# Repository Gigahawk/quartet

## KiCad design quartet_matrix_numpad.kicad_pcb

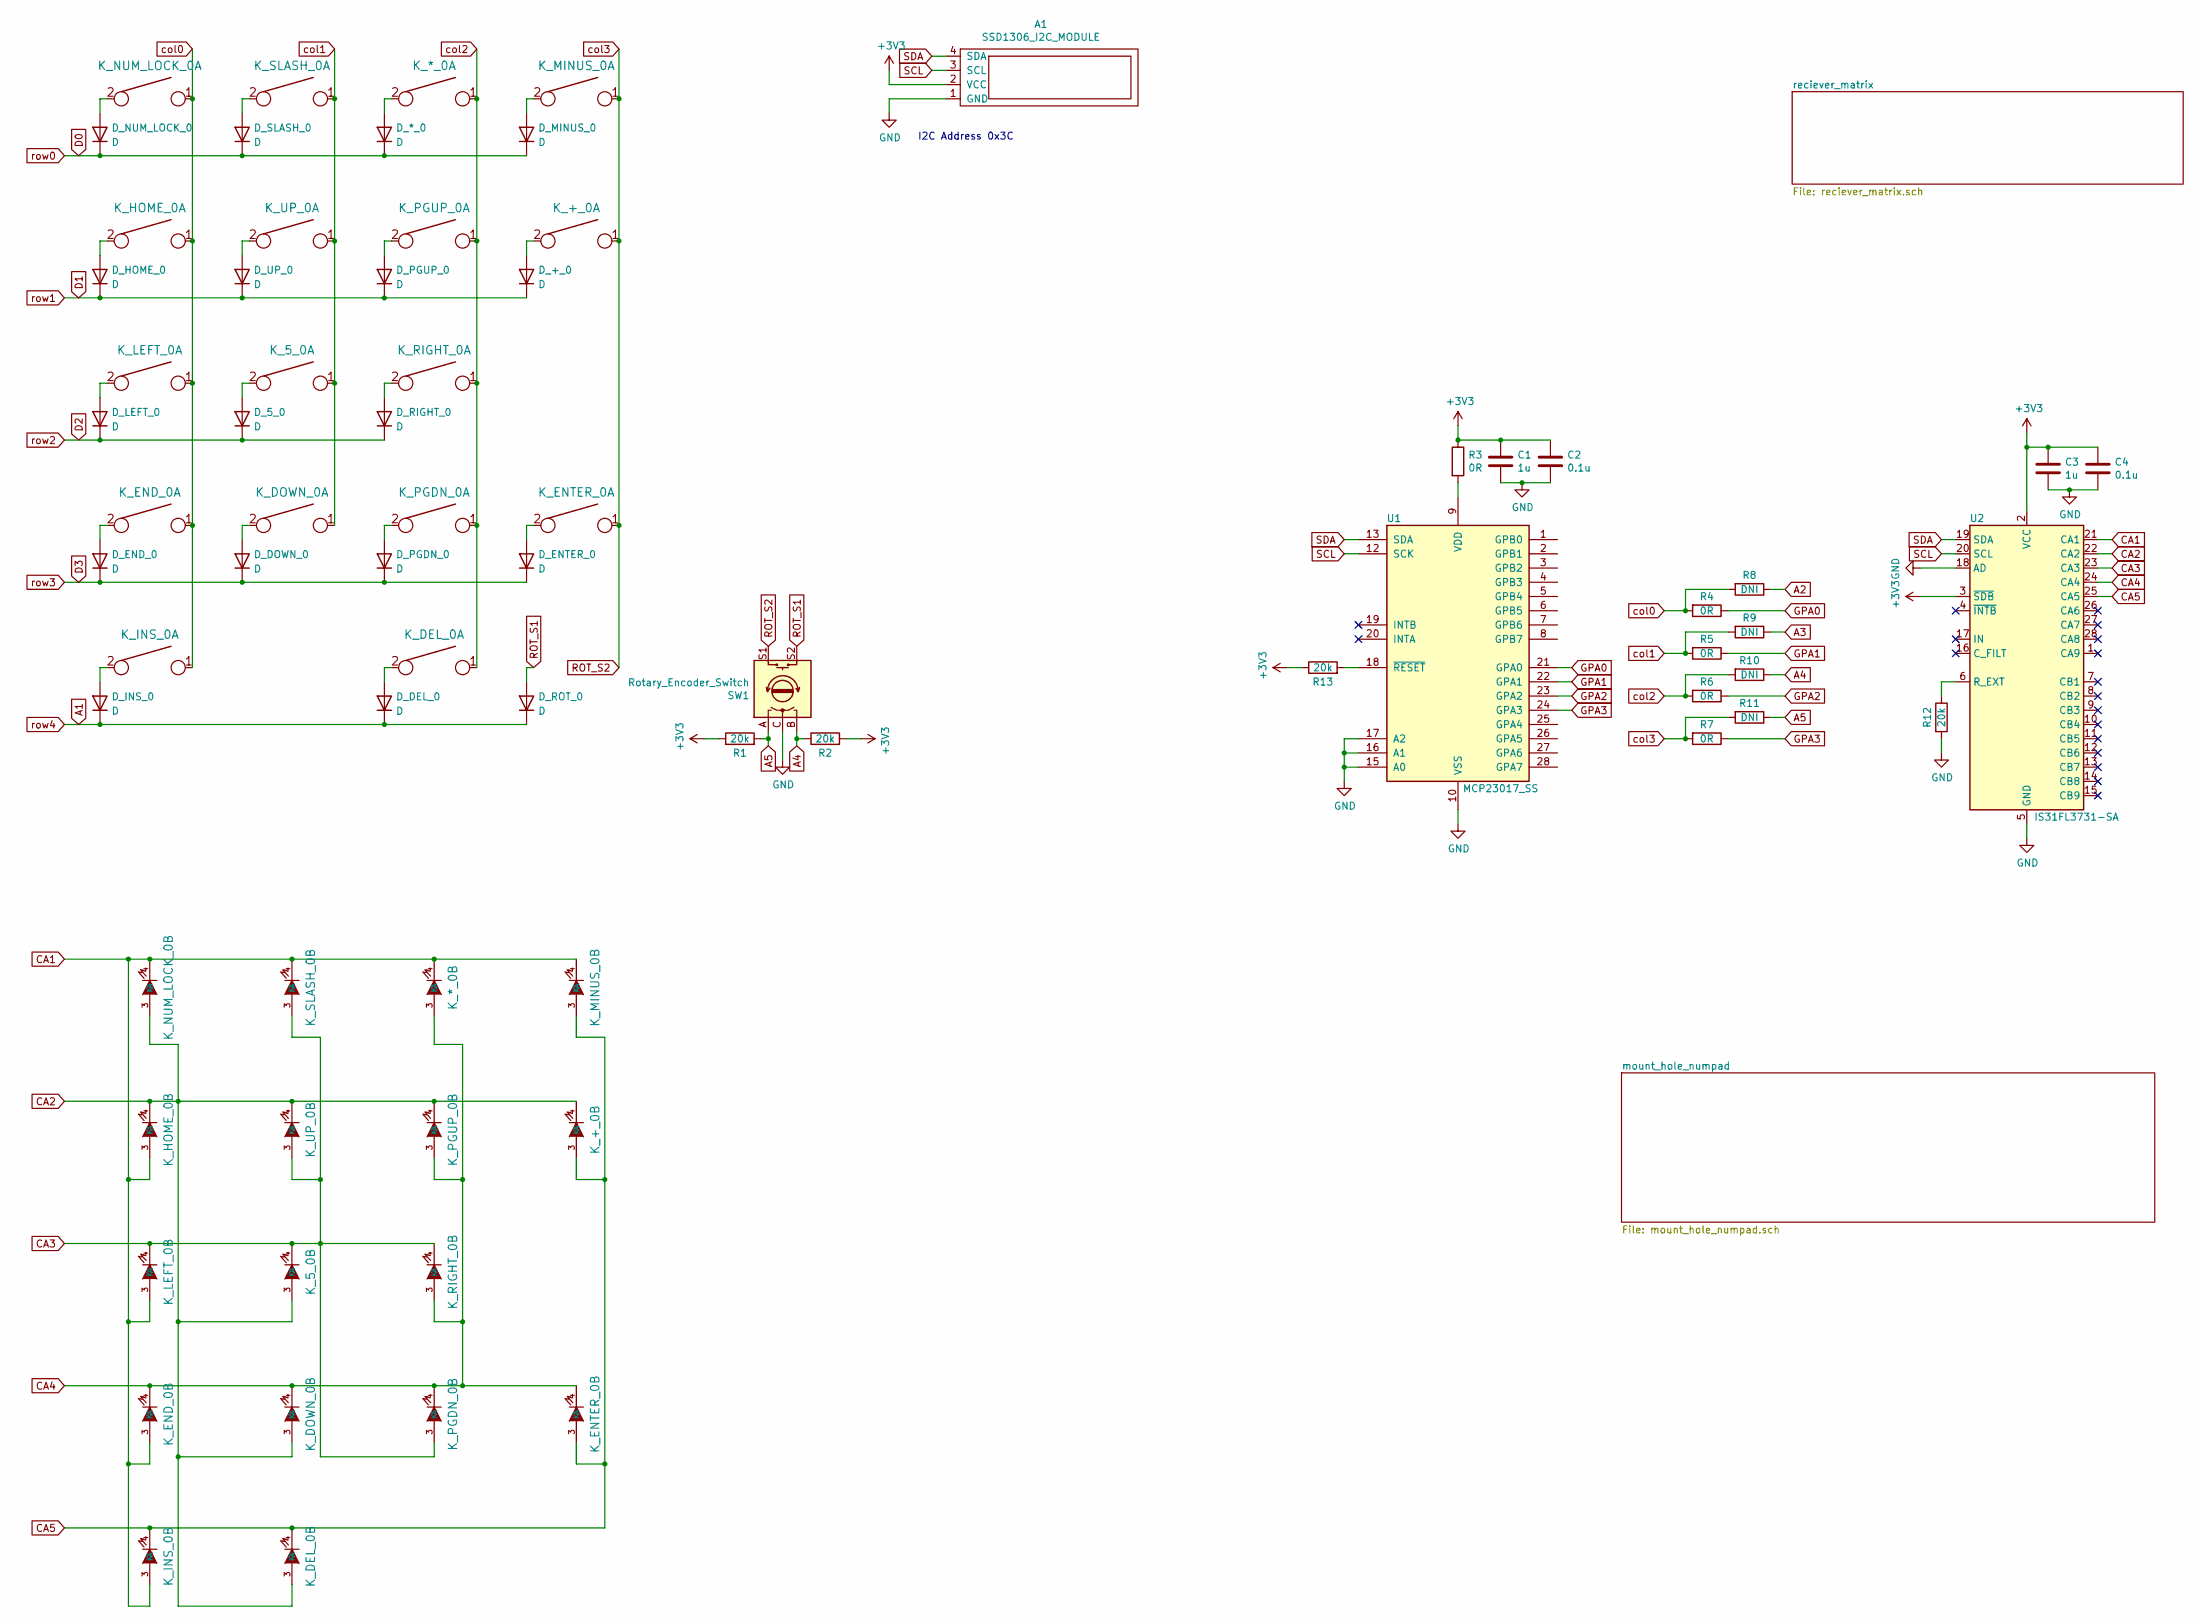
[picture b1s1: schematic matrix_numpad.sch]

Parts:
A1: SSD1306_I2C_MODULE; SSD1306_MODULE_128x32
C1, C3: 1u; C_0805_2012Metric_Pad1.15x1.40mm_HandSolder
C2, C4: 0.1u; C_0805_2012Metric_Pad1.15x1.40mm_HandSolder
D_5_0: D; D_SOD123_axial
D_*_0: D; D_SOD123_axial
D_+_0: D; D_SOD123_axial
D_DEL_0: D; D_SOD123_axial
D_DOWN_0: D; D_SOD123_axial
D_END_0: D; D_SOD123_axial
D_ENTER_0: D; D_SOD123_axial
D_HOME_0: D; D_SOD123_axial
D_INS_0: D; D_SOD123_axial
D_LEFT_0: D; D_SOD123_axial
D_MINUS_0: D; D_SOD123_axial
D_NUM_LOCK_0: D; D_SOD123_axial
D_PGDN_0: D; D_SOD123_axial
D_PGUP_0: D; D_SOD123_axial
D_RIGHT_0: D; D_SOD123_axial
D_ROT_0: D; D_SOD123_axial
D_SLASH_0: D; D_SOD123_axial
D_UP_0: D; D_SOD123_axial
K_5_0: KEYSW; MX-1U
K_*_0: KEYSW; MX-1U
K_+_0: KEYSW; MX-2U
K_DEL_0: KEYSW; MX-1U
K_DOWN_0: KEYSW; MX-1U
K_END_0: KEYSW; MX-1U
K_ENTER_0: KEYSW; MX-2U
K_HOME_0: KEYSW; MX-1U
K_INS_0: KEYSW; MX-2U
K_LEFT_0: KEYSW; MX-1U
K_MINUS_0: KEYSW; MX-1U
K_NUM_LOCK_0: KEYSW; MX-1U
K_PGDN_0: KEYSW; MX-1U
K_PGUP_0: KEYSW; MX-1U
K_RIGHT_0: KEYSW; MX-1U
K_SLASH_0: KEYSW; MX-1U
K_UP_0: KEYSW; MX-1U
R1, R2, R12, R13: 20k; R_0805_2012Metric_Pad1.15x1.40mm_HandSolder
R3, R4, R5, R6, R7: 0R; R_0805_2012Metric_Pad1.15x1.40mm_HandSolder
R8, R9, R10, R11: DNI; R_0805_2012Metric_Pad1.15x1.40mm_HandSolder
SW1: Rotary_Encoder_Switch; 482016514001
U1: MCP23017_SS; SSOP-28_5.3x10.2mm_P0.65mm
U2: IS31FL3731-SA; SSOP-28_5.3x10.2mm_P0.65mm

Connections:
+3V3: A1.2 (VCC), C1.1, C2.1, C3.1, C4.1, R1.1, R2.2, R3.1, R13.1, U2.2 (VCC), U2.3 (~SDB); also elsewhere on the board
A1: D_DEL_0.1 (K), D_INS_0.1 (K), D_ROT_0.1 (K); also elsewhere on the board
A2: R8.1; also elsewhere on the board
A3: R9.1; also elsewhere on the board
A4: R2.1, R10.1, SW1.B; also elsewhere on the board
A5: R1.2, R11.1, SW1.A; also elsewhere on the board
CA1: K_*_0.4 (K), K_END_0.3 (A), K_HOME_0.3 (A), K_INS_0.3 (A), K_LEFT_0.3 (A), K_MINUS_0.4 (K), K_NUM_LOCK_0.4 (K), K_SLASH_0.4 (K), U2.21 (CA1)
CA2: K_5_0.3 (A), K_+_0.4 (K), K_DEL_0.3 (A), K_DOWN_0.3 (A), K_HOME_0.4 (K), K_NUM_LOCK_0.3 (A), K_PGUP_0.4 (K), K_UP_0.4 (K), U2.22 (CA2)
CA3: K_5_0.4 (K), K_LEFT_0.4 (K), K_PGDN_0.3 (A), K_RIGHT_0.4 (K), K_SLASH_0.3 (A), K_UP_0.3 (A), U2.23 (CA3)
CA4: K_*_0.3 (A), K_DOWN_0.4 (K), K_END_0.4 (K), K_ENTER_0.4 (K), K_PGDN_0.4 (K), K_PGUP_0.3 (A), K_RIGHT_0.3 (A), U2.24 (CA4)
CA5: K_+_0.3 (A), K_DEL_0.4 (K), K_ENTER_0.3 (A), K_INS_0.4 (K), K_MINUS_0.3 (A), U2.25 (CA5)
D0: D_*_0.1 (K), D_MINUS_0.1 (K), D_NUM_LOCK_0.1 (K), D_SLASH_0.1 (K); also elsewhere on the board
D1: D_+_0.1 (K), D_HOME_0.1 (K), D_PGUP_0.1 (K), D_UP_0.1 (K); also elsewhere on the board
D2: D_5_0.1 (K), D_LEFT_0.1 (K), D_RIGHT_0.1 (K); also elsewhere on the board
D3: D_DOWN_0.1 (K), D_END_0.1 (K), D_ENTER_0.1 (K), D_PGDN_0.1 (K); also elsewhere on the board
GND: A1.1 (GND), C1.2, C2.2, C3.2, C4.2, R12.2, SW1.C, U1.10 (VSS), U1.15 (A0), U1.16 (A1), U1.17 (A2), U2.5 (GND), U2.18 (AD); also elsewhere on the board
GPA0: R4.1, U1.21 (GPA0)
GPA1: R5.1, U1.22 (GPA1)
GPA2: R6.1, U1.23 (GPA2)
GPA3: R7.1, U1.24 (GPA3)
unnamed: D_5_0.2 (A), K_5_0.2
unnamed: D_*_0.2 (A), K_*_0.2
unnamed: D_+_0.2 (A), K_+_0.2
unnamed: D_DEL_0.2 (A), K_DEL_0.2
unnamed: D_DOWN_0.2 (A), K_DOWN_0.2
unnamed: D_END_0.2 (A), K_END_0.2
unnamed: D_ENTER_0.2 (A), K_ENTER_0.2
unnamed: D_HOME_0.2 (A), K_HOME_0.2
unnamed: D_INS_0.2 (A), K_INS_0.2
unnamed: D_LEFT_0.2 (A), K_LEFT_0.2
unnamed: D_MINUS_0.2 (A), K_MINUS_0.2
unnamed: D_NUM_LOCK_0.2 (A), K_NUM_LOCK_0.2
unnamed: D_PGDN_0.2 (A), K_PGDN_0.2
unnamed: D_PGUP_0.2 (A), K_PGUP_0.2
unnamed: D_RIGHT_0.2 (A), K_RIGHT_0.2
unnamed: D_SLASH_0.2 (A), K_SLASH_0.2
unnamed: D_UP_0.2 (A), K_UP_0.2
unnamed: R3.2, U1.9 (VDD)
unnamed: R12.1, U2.6 (R_EXT)
unnamed: R13.2, U1.18 (~RESET~)
ROT_S1: D_ROT_0.2 (A), SW1.S2
ROT_S2: K_+_0.1, K_ENTER_0.1, K_MINUS_0.1, R7.2, R11.2, SW1.S1
SCL: A1.3 (SCL), U1.12 (SCK), U2.20 (SCL); also elsewhere on the board
SDA: A1.4 (SDA), U1.13 (SDA), U2.19 (SDA); also elsewhere on the board
col0: K_END_0.1, K_HOME_0.1, K_INS_0.1, K_LEFT_0.1, K_NUM_LOCK_0.1, R4.2, R8.2
col1: K_5_0.1, K_DOWN_0.1, K_SLASH_0.1, K_UP_0.1, R5.2, R9.2
col2: K_*_0.1, K_DEL_0.1, K_PGDN_0.1, K_PGUP_0.1, K_RIGHT_0.1, R6.2, R10.2

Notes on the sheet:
I2C Address 0x3C

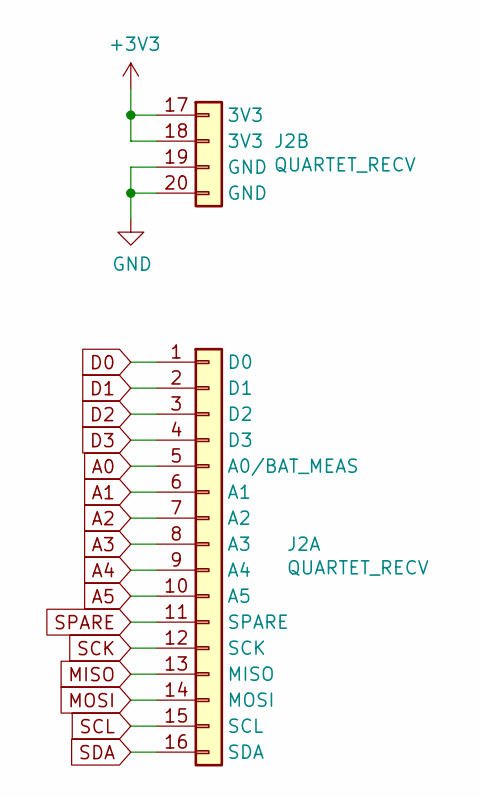
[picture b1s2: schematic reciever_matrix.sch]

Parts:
J2: QUARTET_RECV; QUARTET_RECV_MATRIX; Part Numbers F519-1A7A1-11004-E200; F519-1A7A1-11016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

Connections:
+3V3: J2.17 (3V3), J2.18 (3V3); also elsewhere on the board
A0: J2.5 (A0/BAT_MEAS)
A1: J2.6 (A1); also elsewhere on the board
A2: J2.7 (A2); also elsewhere on the board
A3: J2.8 (A3); also elsewhere on the board
A4: J2.9 (A4); also elsewhere on the board
A5: J2.10 (A5); also elsewhere on the board
D0: J2.1 (D0); also elsewhere on the board
D1: J2.2 (D1); also elsewhere on the board
D2: J2.3 (D2); also elsewhere on the board
D3: J2.4 (D3); also elsewhere on the board
GND: J2.19 (GND), J2.20 (GND); also elsewhere on the board
MISO: J2.13 (MISO)
MOSI: J2.14 (MOSI)
SCK: J2.12 (SCK)
SCL: J2.15 (SCL); also elsewhere on the board
SDA: J2.16 (SDA); also elsewhere on the board
SPARE: J2.11 (SPARE)

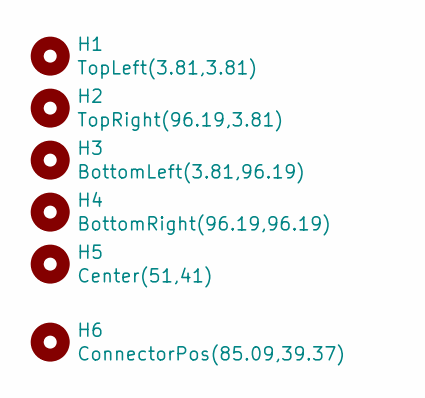
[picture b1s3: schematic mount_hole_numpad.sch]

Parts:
H1: TopLeft(3.81,3.81); MountingHole_2.2mm_M2_Pad
H2: TopRight(96.19,3.81); MountingHole_2.2mm_M2_Pad
H3: BottomLeft(3.81,96.19); MountingHole_2.2mm_M2_Pad
H4: BottomRight(96.19,96.19); MountingHole_2.2mm_M2_Pad
H5: Center(51,41); MountingHole_2.2mm_M2_Pad
H6: ConnectorPos(85.09,39.37); DOT

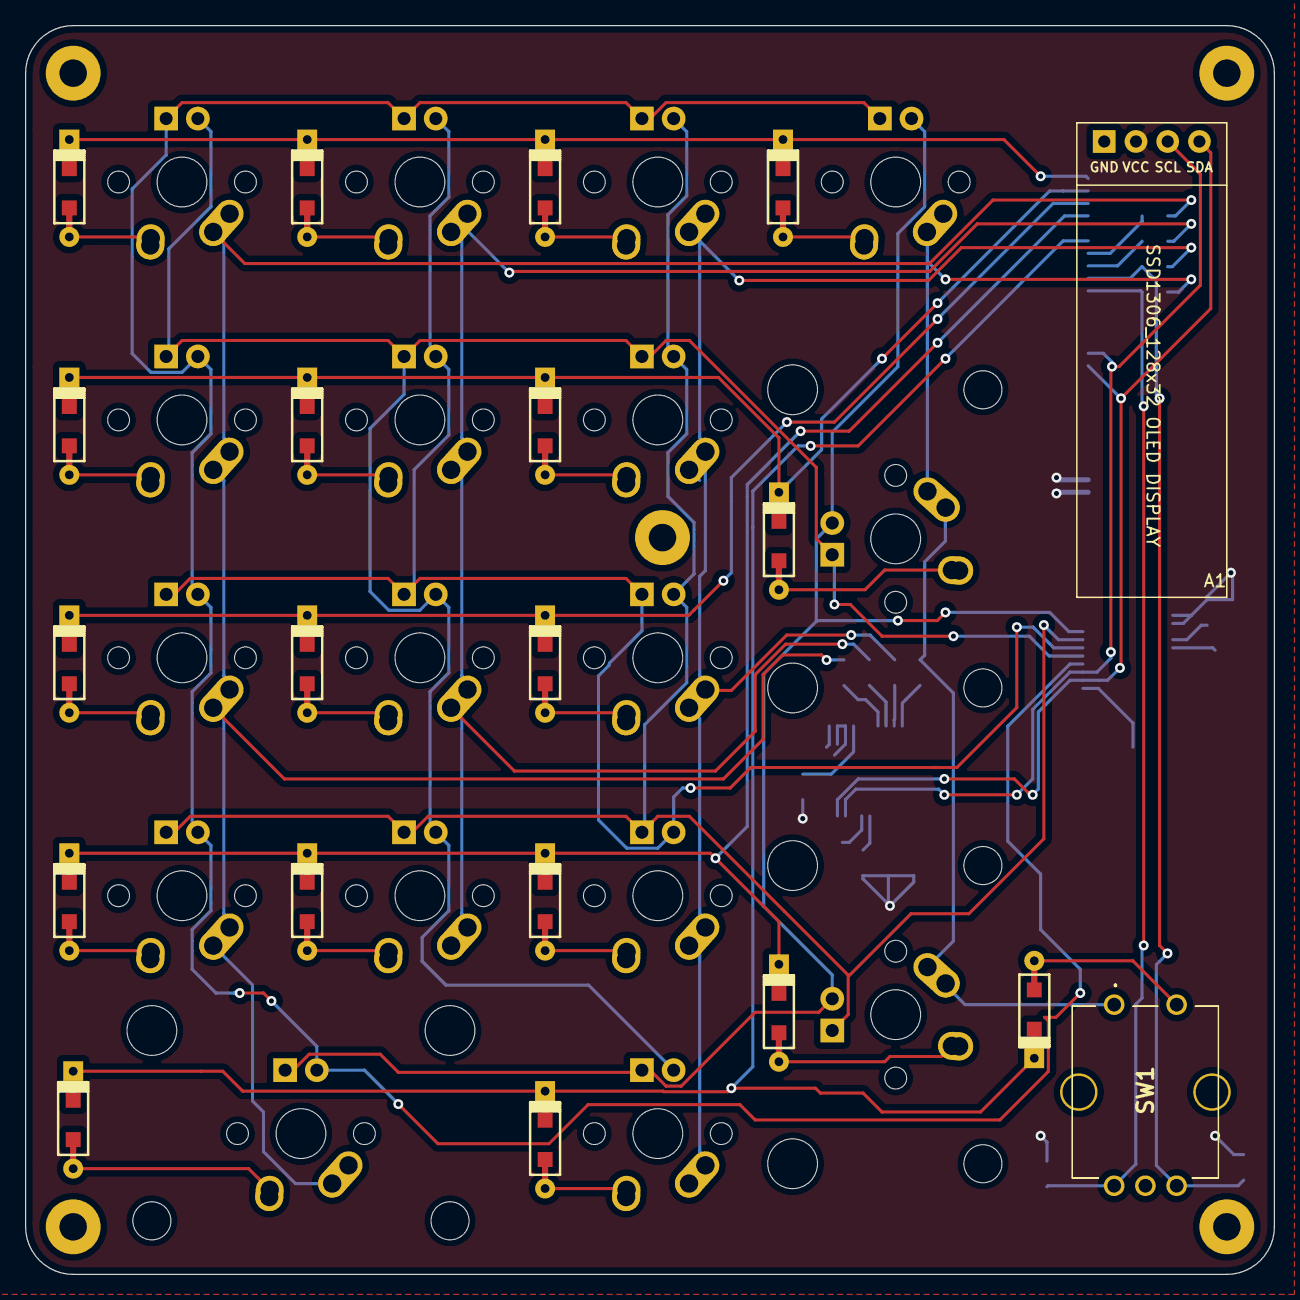
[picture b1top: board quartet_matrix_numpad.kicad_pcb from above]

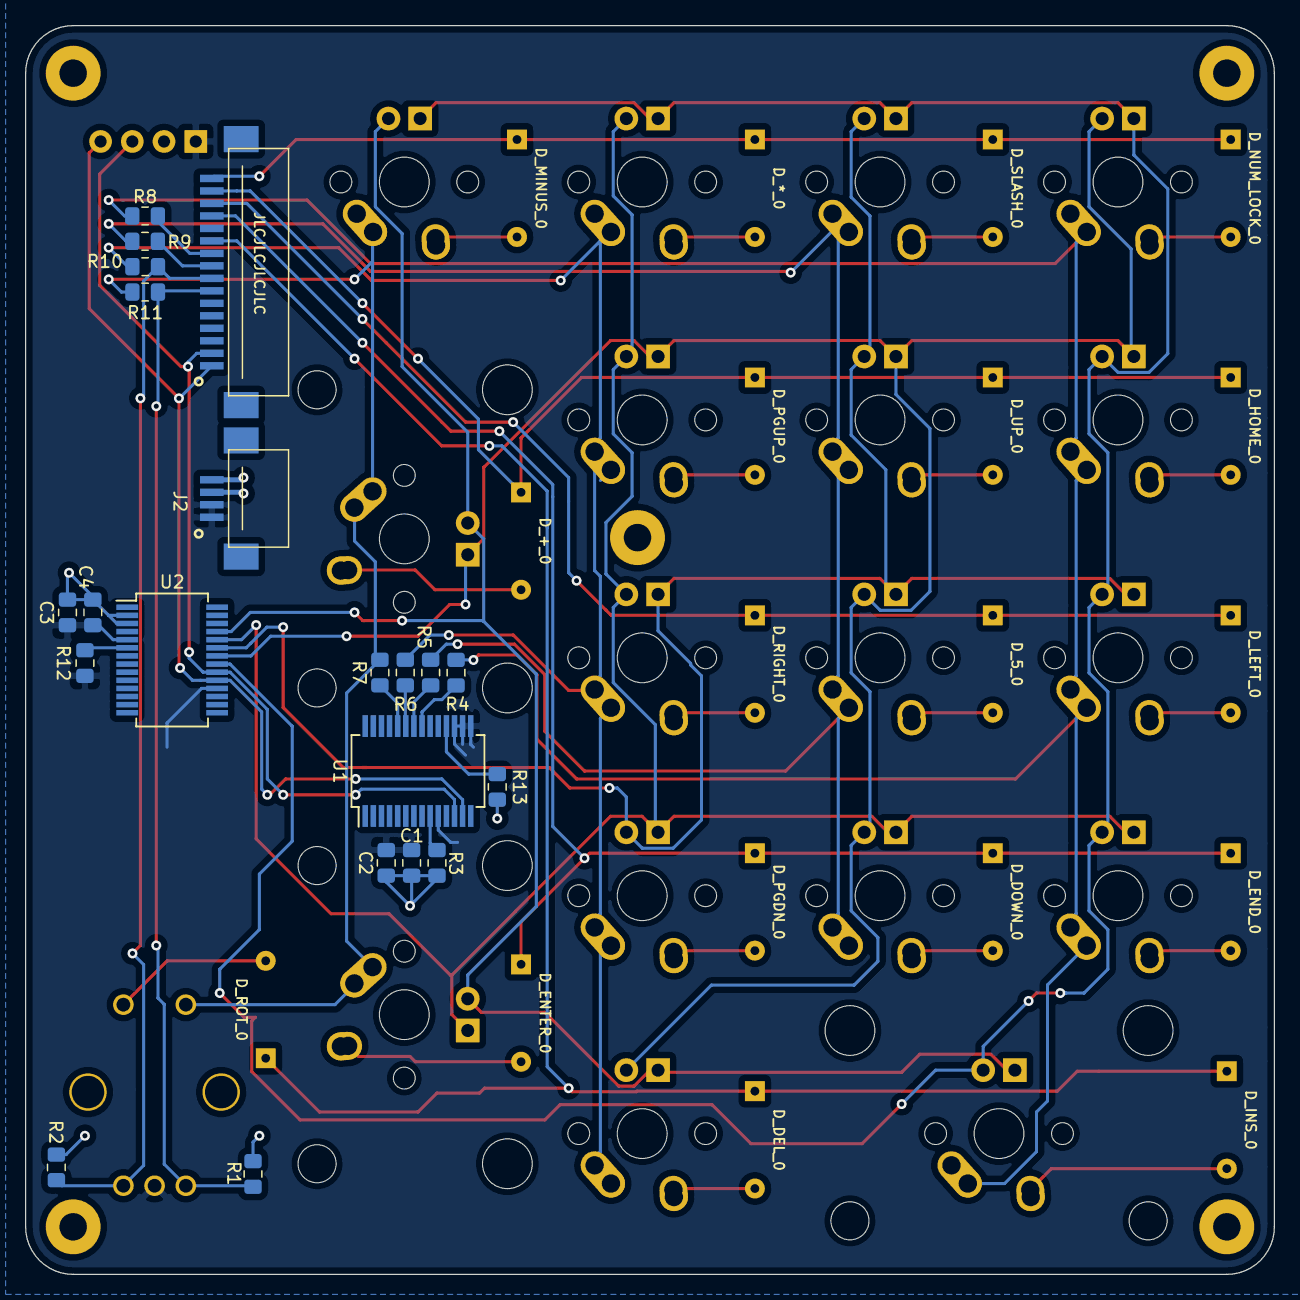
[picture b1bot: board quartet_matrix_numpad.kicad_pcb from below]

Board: 2 copper layers, 100.0 x 100.0 mm, 63 parts (20 on the bottom side), 47 nets.

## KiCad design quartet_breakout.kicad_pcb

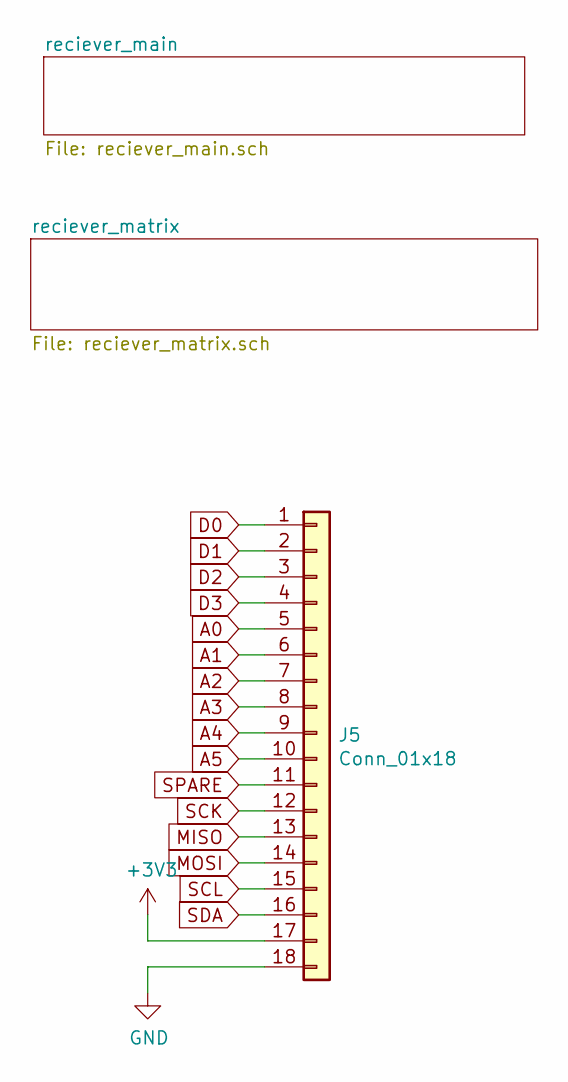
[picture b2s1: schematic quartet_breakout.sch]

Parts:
J5: Conn_01x18; PinHeader_1x18_P2.54mm_Vertical

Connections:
+3V3: J5.17; also elsewhere on the board
A0: J5.5; also elsewhere on the board
A1: J5.6; also elsewhere on the board
A2: J5.7; also elsewhere on the board
A3: J5.8; also elsewhere on the board
A4: J5.9; also elsewhere on the board
A5: J5.10; also elsewhere on the board
D0: J5.1; also elsewhere on the board
D1: J5.2; also elsewhere on the board
D2: J5.3; also elsewhere on the board
D3: J5.4; also elsewhere on the board
GND: J5.18; also elsewhere on the board
MISO: J5.13; also elsewhere on the board
MOSI: J5.14; also elsewhere on the board
SCK: J5.12; also elsewhere on the board
SCL: J5.15; also elsewhere on the board
SDA: J5.16; also elsewhere on the board
SPARE: J5.11; also elsewhere on the board

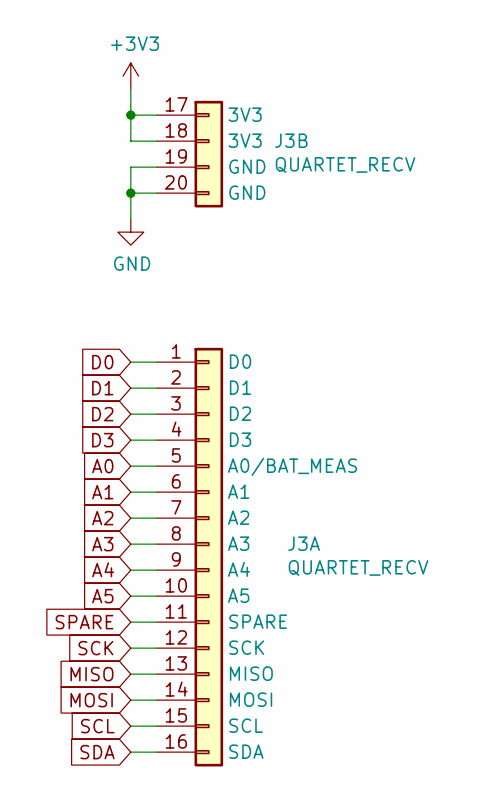
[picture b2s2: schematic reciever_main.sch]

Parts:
J3: QUARTET_RECV; QUARTET_RECV_MAIN; Part Numbers F519-1A7A1-11004-E200; F519-1A7A1-11016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

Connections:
+3V3: J3.17 (3V3), J3.18 (3V3); also elsewhere on the board
A0: J3.5 (A0/BAT_MEAS); also elsewhere on the board
A1: J3.6 (A1); also elsewhere on the board
A2: J3.7 (A2); also elsewhere on the board
A3: J3.8 (A3); also elsewhere on the board
A4: J3.9 (A4); also elsewhere on the board
A5: J3.10 (A5); also elsewhere on the board
D0: J3.1 (D0); also elsewhere on the board
D1: J3.2 (D1); also elsewhere on the board
D2: J3.3 (D2); also elsewhere on the board
D3: J3.4 (D3); also elsewhere on the board
GND: J3.19 (GND), J3.20 (GND); also elsewhere on the board
MISO: J3.13 (MISO); also elsewhere on the board
MOSI: J3.14 (MOSI); also elsewhere on the board
SCK: J3.12 (SCK); also elsewhere on the board
SCL: J3.15 (SCL); also elsewhere on the board
SDA: J3.16 (SDA); also elsewhere on the board
SPARE: J3.11 (SPARE); also elsewhere on the board

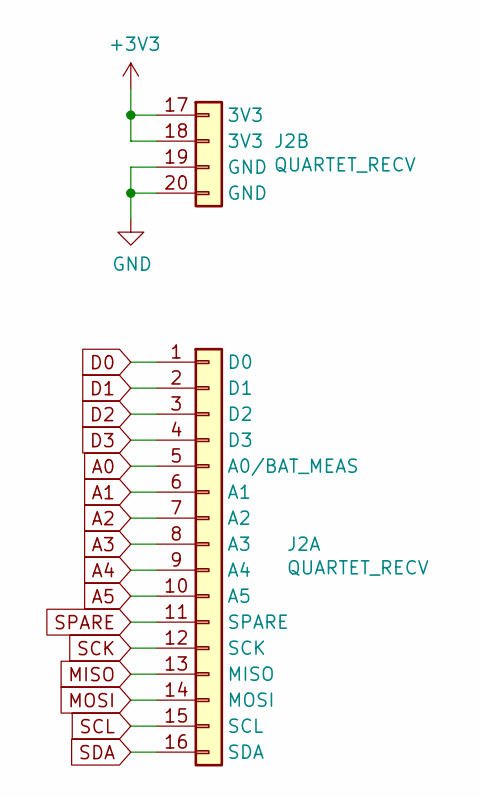
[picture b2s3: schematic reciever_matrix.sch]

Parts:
J2: QUARTET_RECV; QUARTET_RECV_MATRIX; Part Numbers F519-1A7A1-11004-E200; F519-1A7A1-11016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

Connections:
+3V3: J2.17 (3V3), J2.18 (3V3); also elsewhere on the board
A0: J2.5 (A0/BAT_MEAS); also elsewhere on the board
A1: J2.6 (A1); also elsewhere on the board
A2: J2.7 (A2); also elsewhere on the board
A3: J2.8 (A3); also elsewhere on the board
A4: J2.9 (A4); also elsewhere on the board
A5: J2.10 (A5); also elsewhere on the board
D0: J2.1 (D0); also elsewhere on the board
D1: J2.2 (D1); also elsewhere on the board
D2: J2.3 (D2); also elsewhere on the board
D3: J2.4 (D3); also elsewhere on the board
GND: J2.19 (GND), J2.20 (GND); also elsewhere on the board
MISO: J2.13 (MISO); also elsewhere on the board
MOSI: J2.14 (MOSI); also elsewhere on the board
SCK: J2.12 (SCK); also elsewhere on the board
SCL: J2.15 (SCL); also elsewhere on the board
SDA: J2.16 (SDA); also elsewhere on the board
SPARE: J2.11 (SPARE); also elsewhere on the board

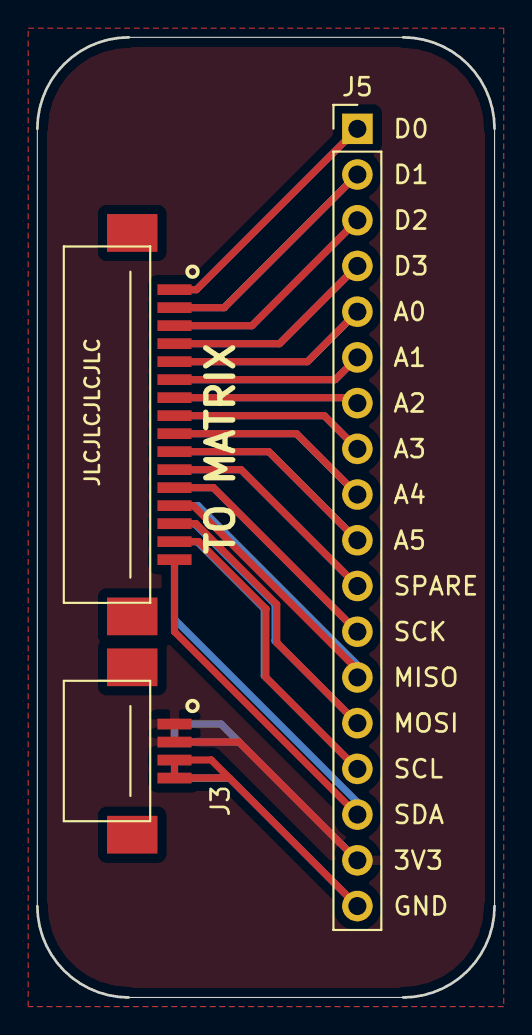
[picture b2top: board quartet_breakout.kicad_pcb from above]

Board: 2 copper layers, 25.4 x 53.3 mm, 3 parts (1 on the bottom side), 18 nets.

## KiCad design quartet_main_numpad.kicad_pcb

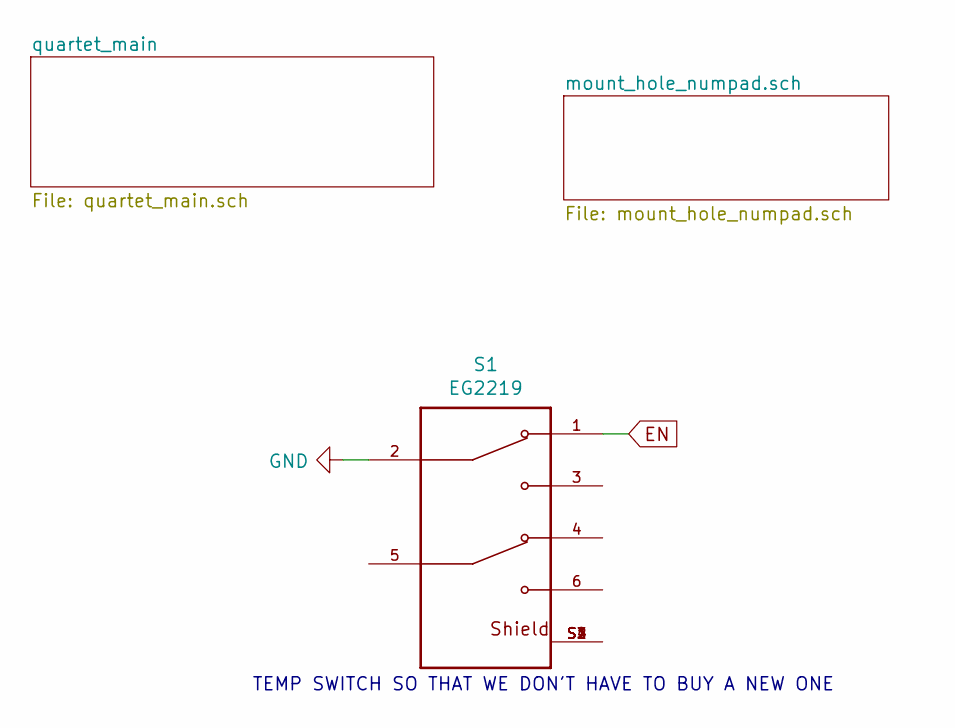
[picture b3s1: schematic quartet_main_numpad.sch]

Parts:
S1: EG2219; SW_EG2219

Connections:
EN: S1.1; also elsewhere on the board
GND: S1.2 (COM_2); also elsewhere on the board
unnamed: S1.S1 (SHIELD), S1.S2 (SHIELD), S1.S3 (SHIELD), S1.S4 (SHIELD)

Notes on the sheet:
TEMP SWITCH SO THAT WE DON'T HAVE TO BUY A NEW ONE

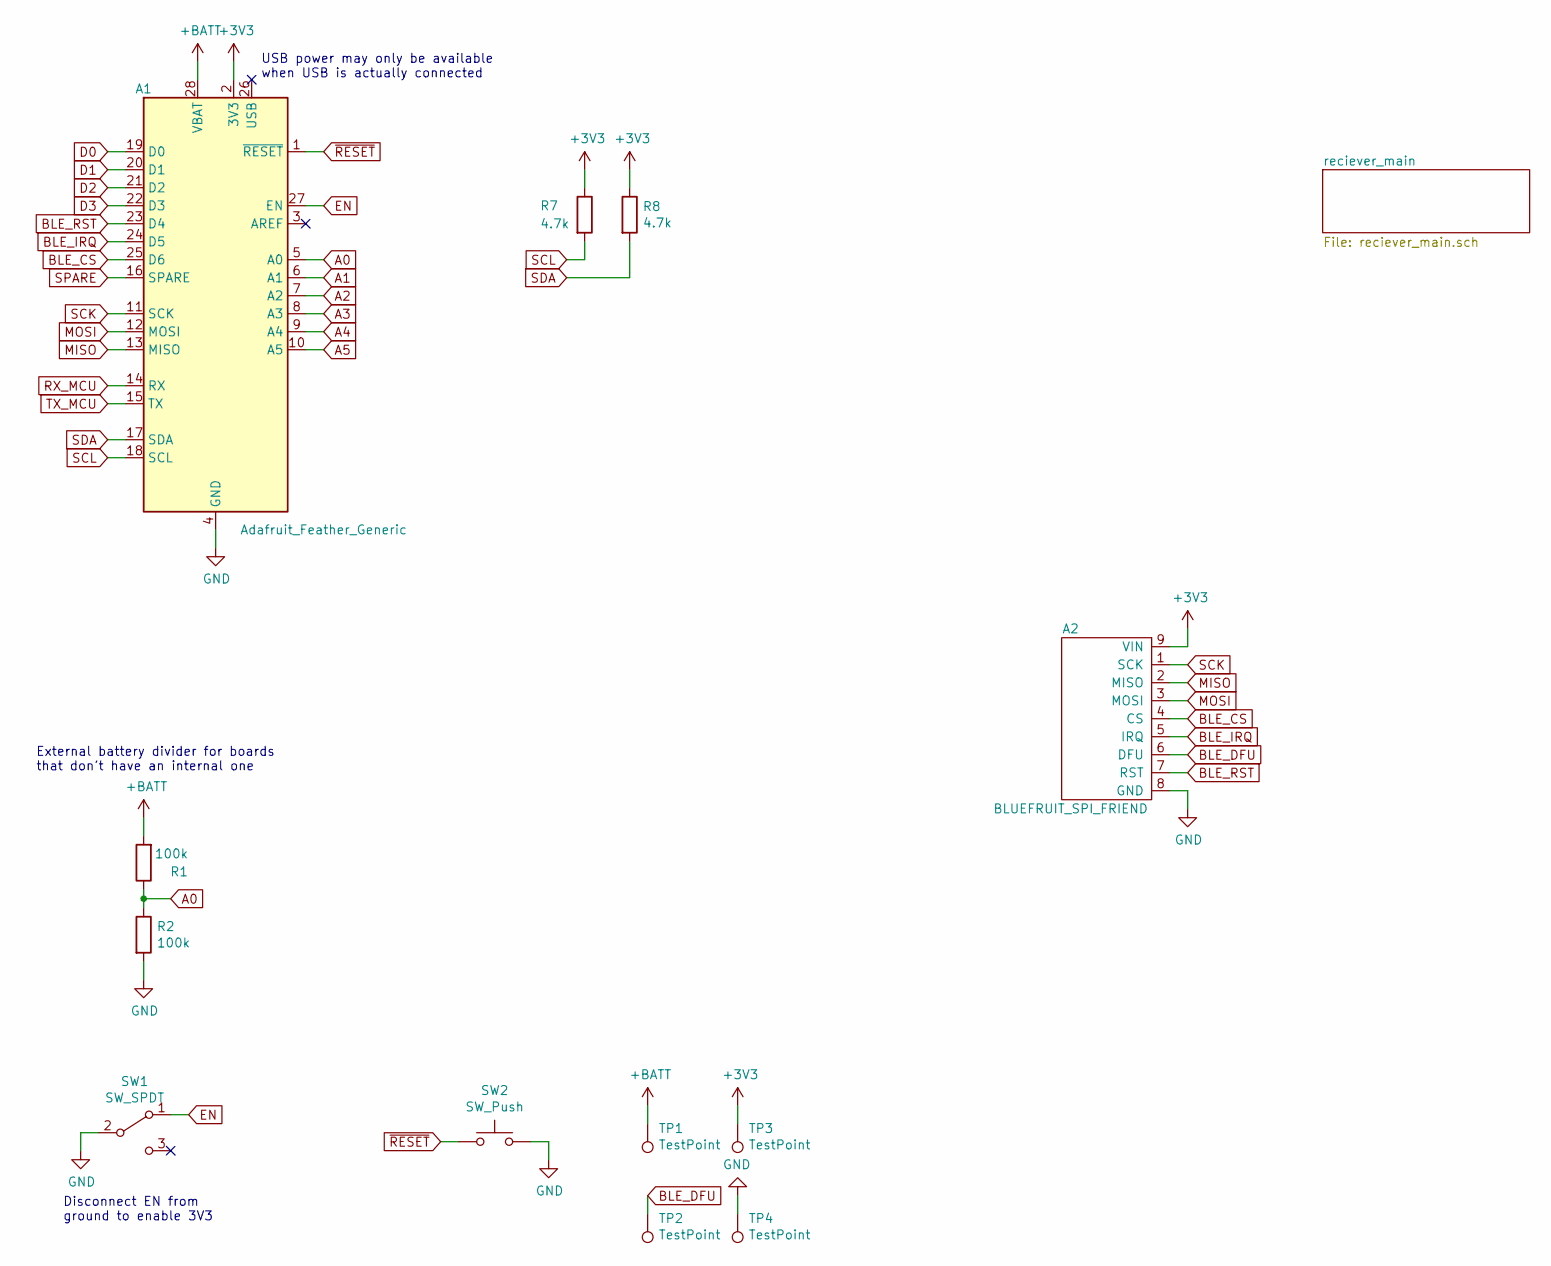
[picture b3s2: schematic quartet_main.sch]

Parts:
A1: Adafruit_Feather_Generic; Adafruit_Feather_LowProfileSocket
A2: BLUEFRUIT_SPI_FRIEND
R1, R2: 100k; R_0805_2012Metric_Pad1.15x1.40mm_HandSolder
R7, R8: 4.7k; R_0805_2012Metric_Pad1.15x1.40mm_HandSolder
SW1: SW_SPDT; SW_E-Switch_EG1224_SPDT_Angled
SW2: SW_Push; SW_SPST_TL3342
TP1, TP2, TP3, TP4: TestPoint; TestPoint_Pad_1.0x1.0mm

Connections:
+3V3: A1.2 (3V3), A2.9 (VIN), R7.1, R8.1, TP3.1; also elsewhere on the board
+BATT: A1.28 (VBAT), R1.2, TP1.1
A0: A1.5 (A0), R1.1, R2.1; also elsewhere on the board
A1: A1.6 (A1); also elsewhere on the board
A2: A1.7 (A2); also elsewhere on the board
A3: A1.8 (A3); also elsewhere on the board
A4: A1.9 (A4); also elsewhere on the board
A5: A1.10 (A5); also elsewhere on the board
BLE_CS: A1.25 (D6), A2.4 (CS)
BLE_DFU: A2.6 (DFU), TP2.1
BLE_IRQ: A1.24 (D5), A2.5 (IRQ)
BLE_RST: A1.23 (D4), A2.7 (RST)
D0: A1.19 (D0); also elsewhere on the board
D1: A1.20 (D1); also elsewhere on the board
D2: A1.21 (D2); also elsewhere on the board
D3: A1.22 (D3); also elsewhere on the board
EN: A1.27 (EN), SW1.1 (A); also elsewhere on the board
GND: A1.4 (GND), A2.8 (GND), R2.2, SW1.2 (B), SW2.2, TP4.1; also elsewhere on the board
MISO: A1.13 (MISO), A2.2 (MISO); also elsewhere on the board
MOSI: A1.12 (MOSI), A2.3 (MOSI); also elsewhere on the board
RX_MCU: A1.14 (RX)
SCK: A1.11 (SCK), A2.1 (SCK); also elsewhere on the board
SCL: A1.18 (SCL), R7.2; also elsewhere on the board
SDA: A1.17 (SDA), R8.2; also elsewhere on the board
SPARE: A1.16 (SPARE); also elsewhere on the board
TX_MCU: A1.15 (TX)
~RESET: A1.1 (~RESET), SW2.1

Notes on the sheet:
USB power may only be available when USB is actually connected
External battery divider for boards that don't have an internal one
Disconnect EN from ground to enable 3V3

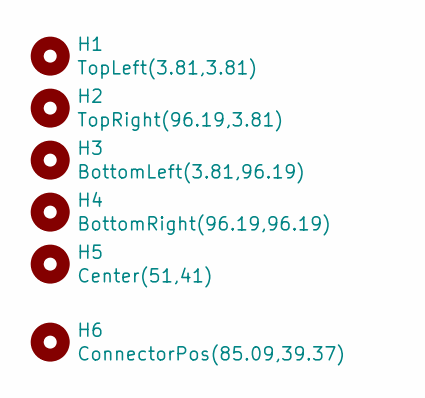
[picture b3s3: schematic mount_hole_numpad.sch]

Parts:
H1: TopLeft(3.81,3.81); MountingHole_2.2mm_M2_Pad
H2: TopRight(96.19,3.81); MountingHole_2.2mm_M2_Pad
H3: BottomLeft(3.81,96.19); MountingHole_2.2mm_M2_Pad
H4: BottomRight(96.19,96.19); MountingHole_2.2mm_M2_Pad
H5: Center(51,41); MountingHole_2.2mm_M2_Pad
H6: ConnectorPos(85.09,39.37); DOT

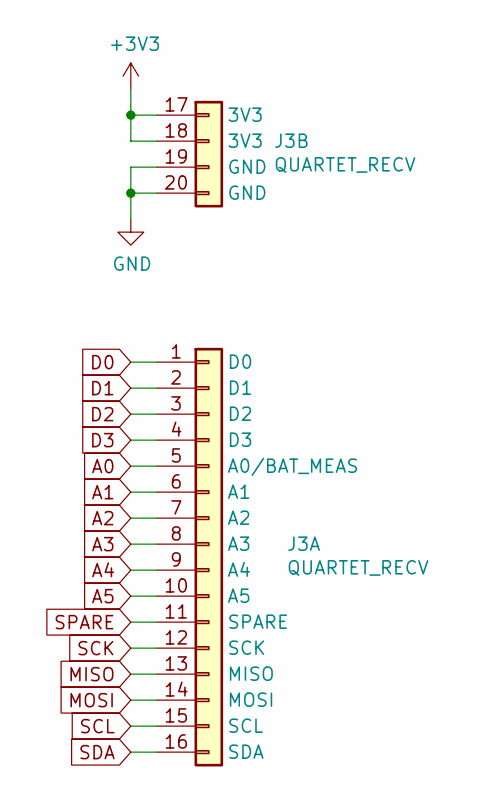
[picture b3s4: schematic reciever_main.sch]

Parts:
J3: QUARTET_RECV; QUARTET_RECV_MAIN; Part Numbers F519-1A7A1-11004-E200; F519-1A7A1-11016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

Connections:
+3V3: J3.17 (3V3), J3.18 (3V3); also elsewhere on the board
A0: J3.5 (A0/BAT_MEAS); also elsewhere on the board
A1: J3.6 (A1); also elsewhere on the board
A2: J3.7 (A2); also elsewhere on the board
A3: J3.8 (A3); also elsewhere on the board
A4: J3.9 (A4); also elsewhere on the board
A5: J3.10 (A5); also elsewhere on the board
D0: J3.1 (D0); also elsewhere on the board
D1: J3.2 (D1); also elsewhere on the board
D2: J3.3 (D2); also elsewhere on the board
D3: J3.4 (D3); also elsewhere on the board
GND: J3.19 (GND), J3.20 (GND); also elsewhere on the board
MISO: J3.13 (MISO); also elsewhere on the board
MOSI: J3.14 (MOSI); also elsewhere on the board
SCK: J3.12 (SCK); also elsewhere on the board
SCL: J3.15 (SCL); also elsewhere on the board
SDA: J3.16 (SDA); also elsewhere on the board
SPARE: J3.11 (SPARE); also elsewhere on the board

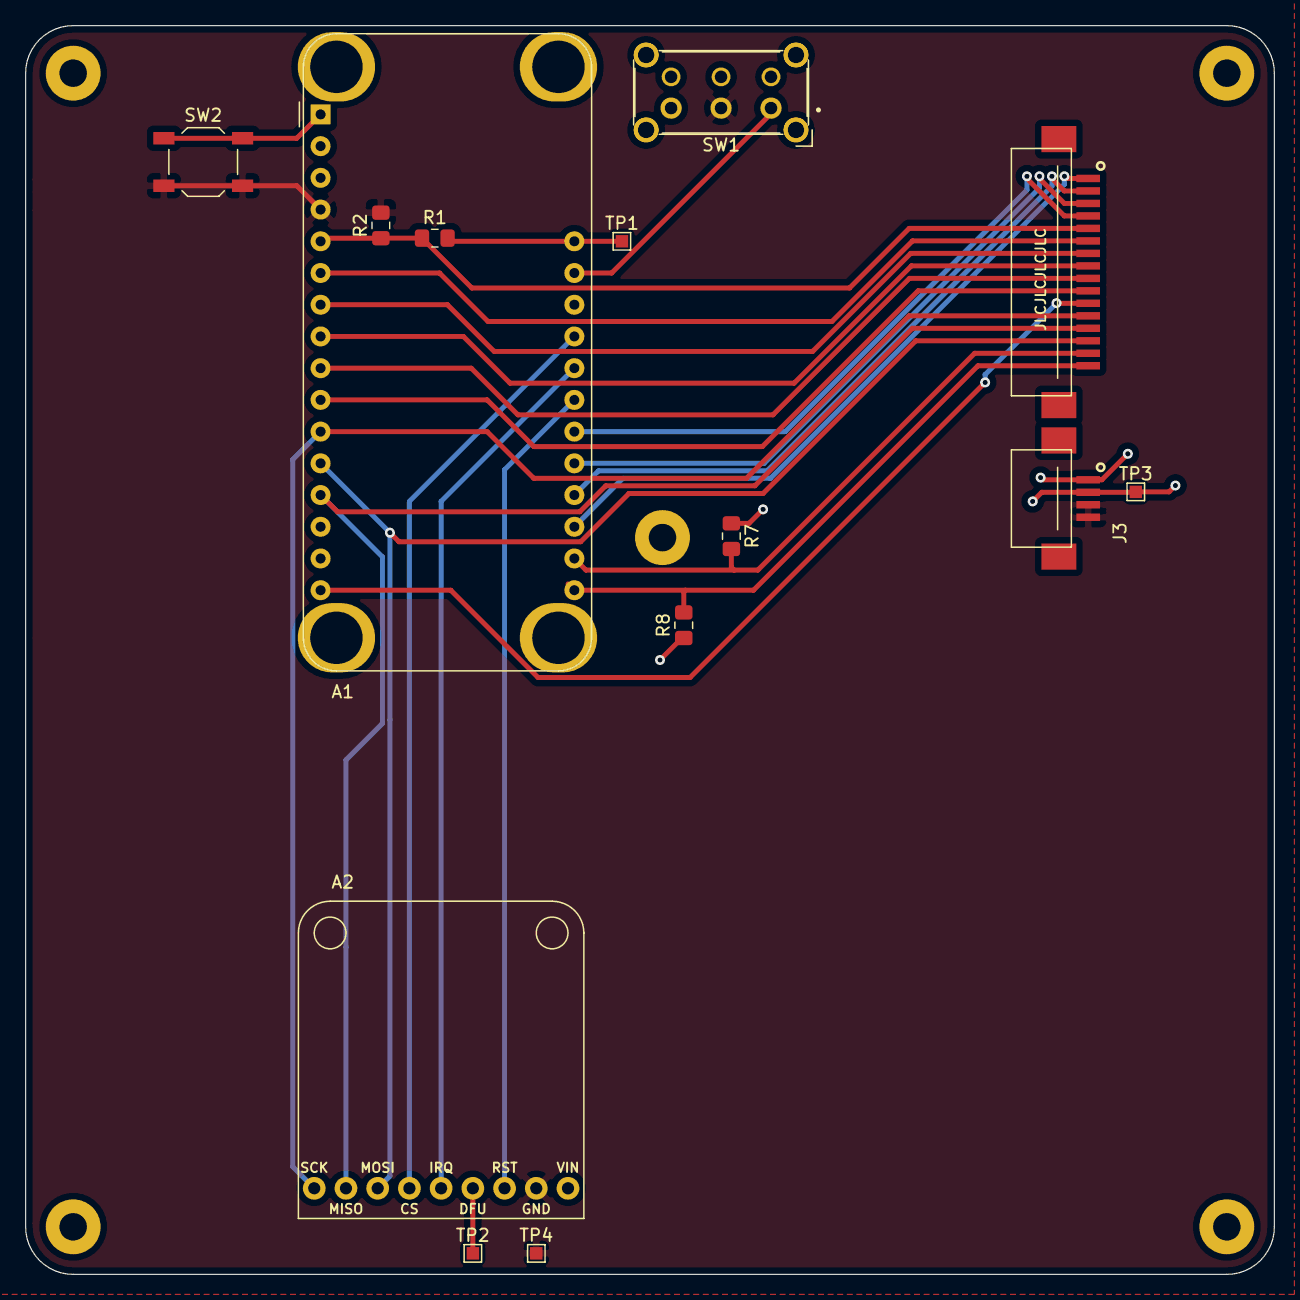
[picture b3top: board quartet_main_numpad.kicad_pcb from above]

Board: 2 copper layers, 100.0 x 100.0 mm, 20 parts (0 on the bottom side), 26 nets.

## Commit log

2021-01-06 First commit, finish most of mainboard schematic
2021-01-07 Move board connectors to separate sheets, create breakout board for testing halves
2021-01-08 Layout and route numpad matrix
2021-03-05 Reroute matrix, redo schematics for feather compat
2021-03-05 Finish and route quartet mainboard
2021-03-14 Move bluefruit module on mainboard to accomodate oversize feathers
2021-03-14 Add model for OLED display
2021-03-14 Add FR4 plate for numpad
2021-04-01 Get ready for JLCPCB
2021-05-15 Update libraries
2021-05-15 Remove soldermask and copper fill
2021-08-31 Fix unconnected IO expander reset
